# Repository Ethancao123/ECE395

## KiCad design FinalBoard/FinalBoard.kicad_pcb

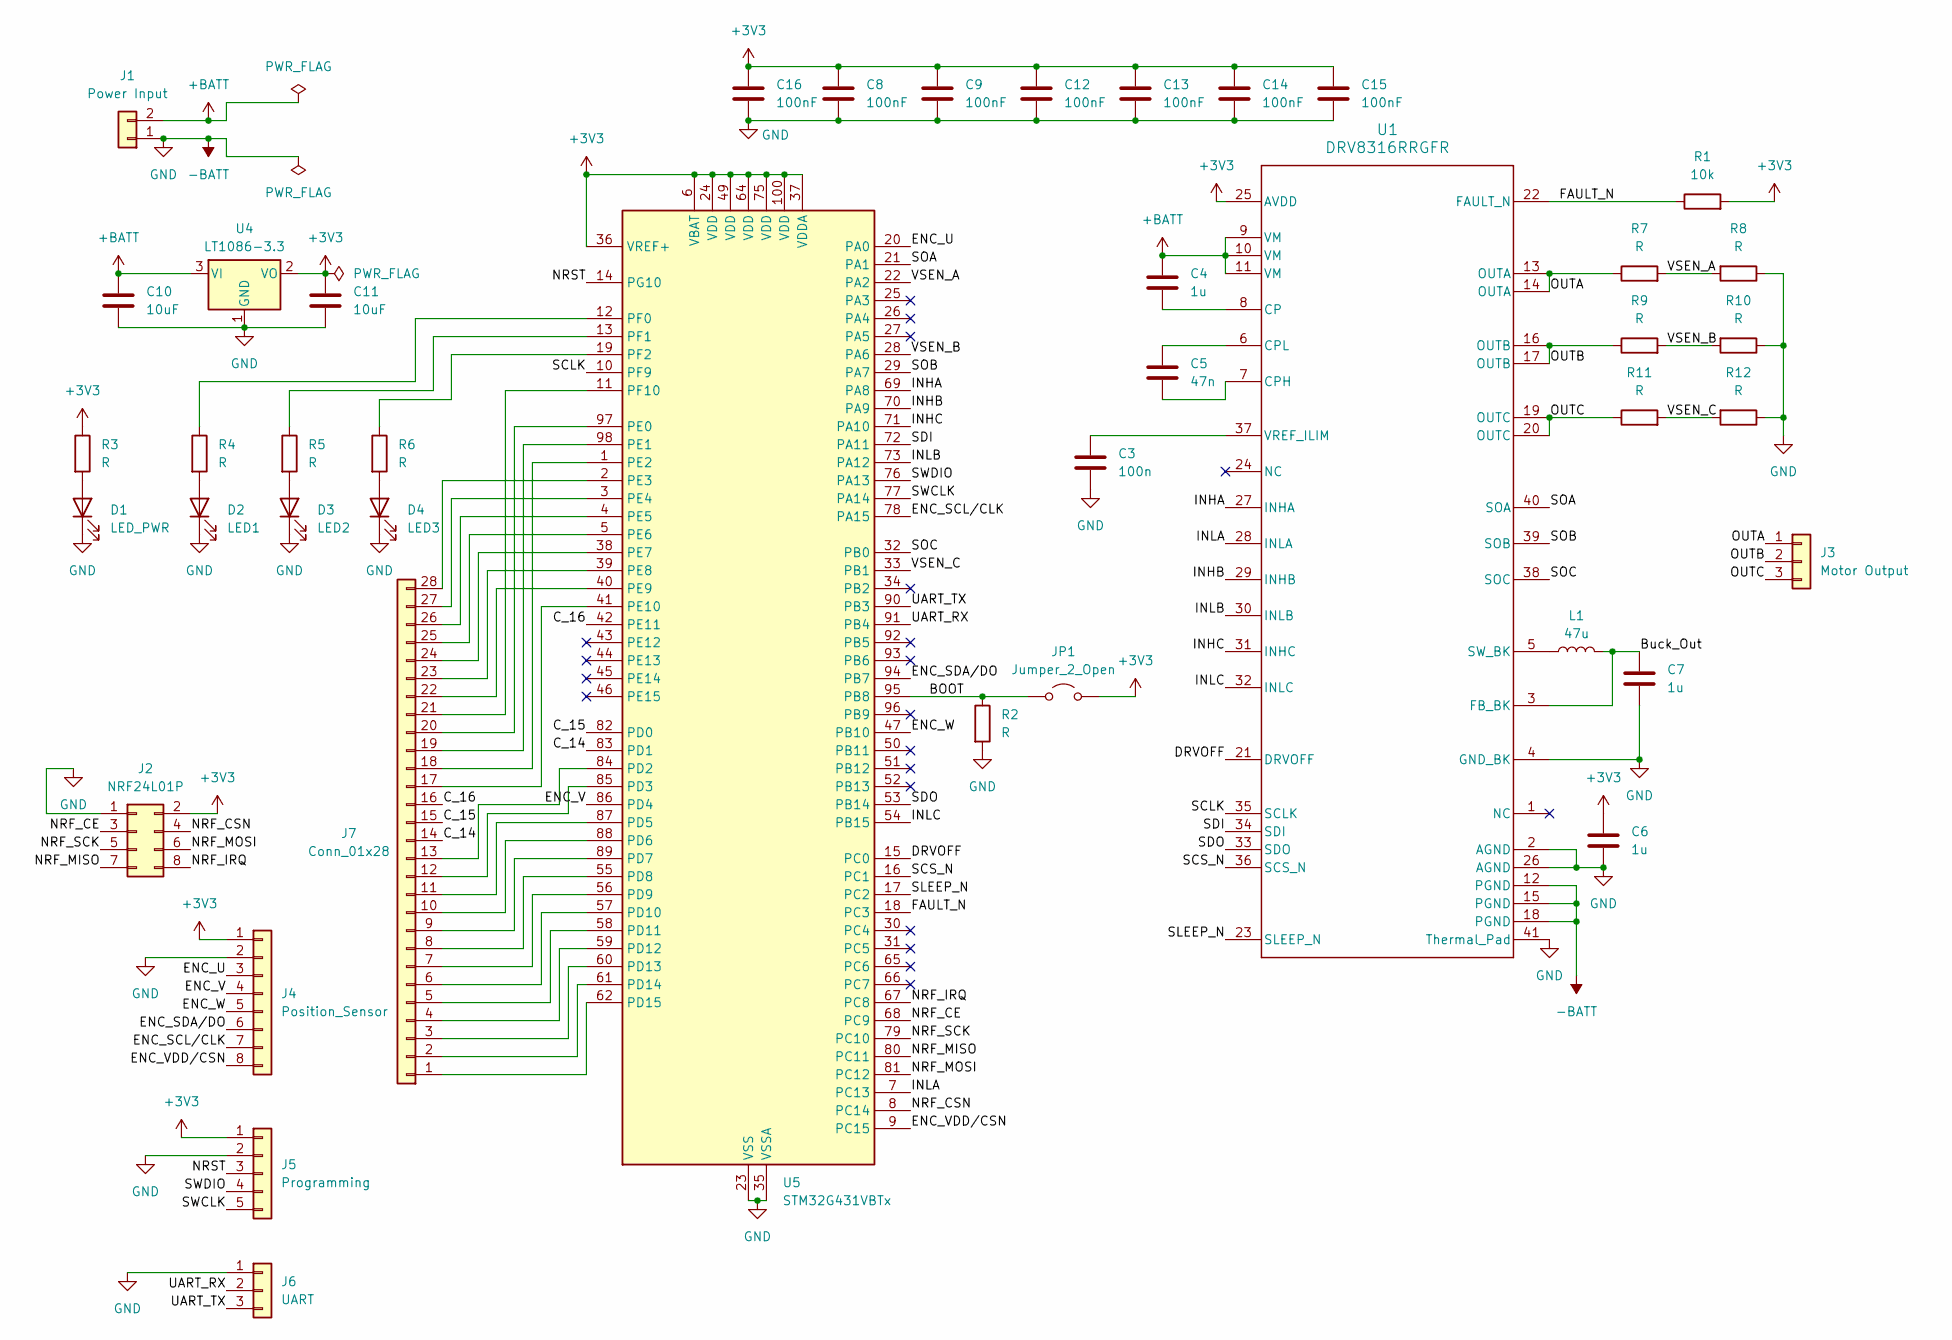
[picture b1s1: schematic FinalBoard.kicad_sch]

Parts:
C3: 100n; C_0805_2012Metric_Pad1.18x1.45mm_HandSolder
C4, C6, C7: 1u; C_0805_2012Metric_Pad1.18x1.45mm_HandSolder
C5: 47n; C_0805_2012Metric_Pad1.18x1.45mm_HandSolder
C8, C9, C12, C13, C14, C15, C16: 100nF; C_0805_2012Metric_Pad1.18x1.45mm_HandSolder
C10, C11: 10uF; CP_EIA-6032-28_Kemet-C_Pad2.25x2.35mm_HandSolder
D1: LED_PWR; LED_2512_6332Metric_Pad1.52x3.35mm_HandSolder
D2: LED1; LED_2512_6332Metric_Pad1.52x3.35mm_HandSolder
D3: LED2; LED_2512_6332Metric_Pad1.52x3.35mm_HandSolder
D4: LED3; LED_2512_6332Metric_Pad1.52x3.35mm_HandSolder
J1: Power Input; AMASS_XT30UPB-M_1x02_P5.0mm_Vertical
J2: NRF24L01P; PinHeader_2x04_P2.54mm_Vertical
J3: Motor Output; PinHeader_1x03_P2.54mm_Vertical
J4: Position_Sensor; PinHeader_1x08_P2.54mm_Vertical
J5: Programming; PinHeader_1x05_P2.54mm_Vertical
J6: UART; PinHeader_1x03_P2.54mm_Vertical
J7: Conn_01x28; PinHeader_1x28_P2.54mm_Vertical
JP1: Jumper_2_Open; SolderJumper-2_P1.3mm_Open_RoundedPad1.0x1.5mm
L1: 47u; L_0603_1608Metric
R1: 10k; R_0805_2012Metric_Pad1.20x1.40mm_HandSolder
R2, R3, R4, R5, R6, R7, R8, R9, R10, R11, R12: R; LED_0805_2012Metric_Pad1.15x1.40mm_HandSolder
U1: DRV8316RRGFR; RGF0040E-IPC_A
U4: LT1086-3.3; TO-220-3_Vertical
U5: STM32G431VBTx; LQFP-100_14x14mm_P0.5mm

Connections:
+3V3: C6.1, C8.1, C9.1, C11.1, C12.1, C13.1, C14.1, C15.1, C16.1, J2.2, J4.1, J5.1, JP1.2 (B), R1.2, R3.1, U1.25 (AVDD), U4.2 (VO), U5.6 (VBAT), U5.24 (VDD), U5.36 (VREF+), U5.37 (VDDA), U5.49 (VDD), U5.64 (VDD), U5.75 (VDD), U5.100 (VDD); also elsewhere on the board
+BATT: C4.1, C10.1, J1.2, U1.9 (VM), U1.10 (VM), U1.11 (VM), U4.3 (VI)
-BATT: C3.2, C6.2, C7.1, C8.2, C9.2, C10.2, C11.2, C12.2, C13.2, C14.2, C15.2, C16.2, D1.1 (K), D2.1 (K), D3.1 (K), D4.1 (K), J1.1, J2.1, J4.2, J5.2, J6.1, R2.2, R8.1, R10.1, R12.1, U1.2 (AGND), U1.4 (GND_BK), U1.12 (PGND), U1.15 (PGND), U1.18 (PGND), U1.26 (AGND), U1.41 (Thermal_Pad), U4.1 (GND), U5.23 (VSS), U5.35 (VSSA), U5.48 (VSS), U5.63 (VSS), U5.74 (VSS), U5.99 (VSS)
/BOOT: JP1.1 (A), R2.1, U5.95 (PB8); also elsewhere on the board
/Buck_Out: C7.2, L1.2, U1.3 (FB_BK)
/C_14: J7.14, U5.83 (PD1)
/C_15: J7.15, U5.82 (PD0)
/C_16: J7.16, U5.42 (PE11)
/DRVOFF: U1.21 (DRVOFF), U5.15 (PC0)
/ENC_SCL/CLK: J4.7, U5.78 (PA15)
/ENC_SDA/DO: J4.6, U5.94 (PB7)
/ENC_U: J4.3, U5.20 (PA0)
/ENC_V: J4.4, U5.86 (PD4)
/ENC_VDD/CSN: J4.8, U5.9 (PC15)
/ENC_W: J4.5, U5.47 (PB10)
/FAULT_N: R1.1, U1.22 (FAULT_N), U5.18 (PC3)
/INHA: U1.27 (INHA), U5.69 (PA8)
/INHB: U1.29 (INHB), U5.70 (PA9)
/INHC: U1.31 (INHC), U5.71 (PA10)
/INLA: U1.28 (INLA), U5.7 (PC13)
/INLB: U1.30 (INLB), U5.73 (PA12)
/INLC: U1.32 (INLC), U5.54 (PB15)
/NRF_CE: J2.3, U5.68 (PC9)
/NRF_CSN: J2.4, U5.8 (PC14)
/NRF_IRQ: J2.8, U5.67 (PC8)
/NRF_MISO: J2.7, U5.80 (PC11)
/NRF_MOSI: J2.6, U5.81 (PC12)
/NRF_SCK: J2.5, U5.79 (PC10)
/NRST: J5.3, U5.14 (PG10)
/OUTA: J3.1, R7.1, U1.13 (OUTA), U1.14 (OUTA)
/OUTB: J3.2, R9.1, U1.16 (OUTB), U1.17 (OUTB)
/OUTC: J3.3, R11.1, U1.19 (OUTC), U1.20 (OUTC)
/SCLK: U1.35 (SCLK), U5.10 (PF9)
/SCS_N: U1.36 (SCS_N), U5.16 (PC1)
/SDI: U1.34 (SDI), U5.72 (PA11)
/SDO: U1.33 (SDO), U5.53 (PB14)
/SLEEP_N: U1.23 (SLEEP_N), U5.17 (PC2)
/SOA: U1.40 (SOA), U5.21 (PA1)
/SOB: U1.39 (SOB), U5.29 (PA7)
/SOC: U1.38 (SOC), U5.32 (PB0)
/SWCLK: J5.5, U5.77 (PA14)
/SWDIO: J5.4, U5.76 (PA13)
/UART_RX: J6.2, U5.91 (PB4)
/UART_TX: J6.3, U5.90 (PB3)
/VSEN_A: R7.2, R8.2, U5.22 (PA2)
/VSEN_B: R9.2, R10.2, U5.28 (PA6)
/VSEN_C: R11.2, R12.2, U5.33 (PB1)
unnamed: D1.2 (A), R3.2
unnamed: D2.2 (A), R4.2
unnamed: D3.2 (A), R5.2
unnamed: D4.2 (A), R6.2
unnamed: J7.1, U5.62 (PD15)
unnamed: J7.2, U5.61 (PD14)
unnamed: J7.3, U5.60 (PD13)
unnamed: J7.4, U5.59 (PD12)
unnamed: J7.5, U5.58 (PD11)
unnamed: J7.6, U5.57 (PD10)
unnamed: J7.7, U5.56 (PD9)
unnamed: J7.8, U5.55 (PD8)
unnamed: J7.9, U5.89 (PD7)
unnamed: J7.10, U5.88 (PD6)
unnamed: J7.11, U5.87 (PD5)
unnamed: J7.12, U5.85 (PD3)
unnamed: J7.13, U5.84 (PD2)
unnamed: J7.17, U5.41 (PE10)
unnamed: J7.18, U5.1 (PE2)
unnamed: J7.19, U5.98 (PE1)
unnamed: J7.20, U5.97 (PE0)
unnamed: J7.21, U5.11 (PF10)
unnamed: J7.22, U5.40 (PE9)
unnamed: J7.23, U5.39 (PE8)
unnamed: J7.24, U5.38 (PE7)
unnamed: J7.25, U5.5 (PE6)
unnamed: J7.26, U5.4 (PE5)
unnamed: J7.27, U5.3 (PE4)
unnamed: J7.28, U5.2 (PE3)
unnamed: C4.2, U1.8 (CP)
unnamed: C5.2, U1.7 (CPH)
unnamed: C5.1, U1.6 (CPL)
unnamed: L1.1, U1.5 (SW_BK)
unnamed: C3.1, U1.37 (VREF_ILIM)
unnamed: R4.1, U5.12 (PF0)
unnamed: R5.1, U5.13 (PF1)
unnamed: R6.1, U5.19 (PF2)

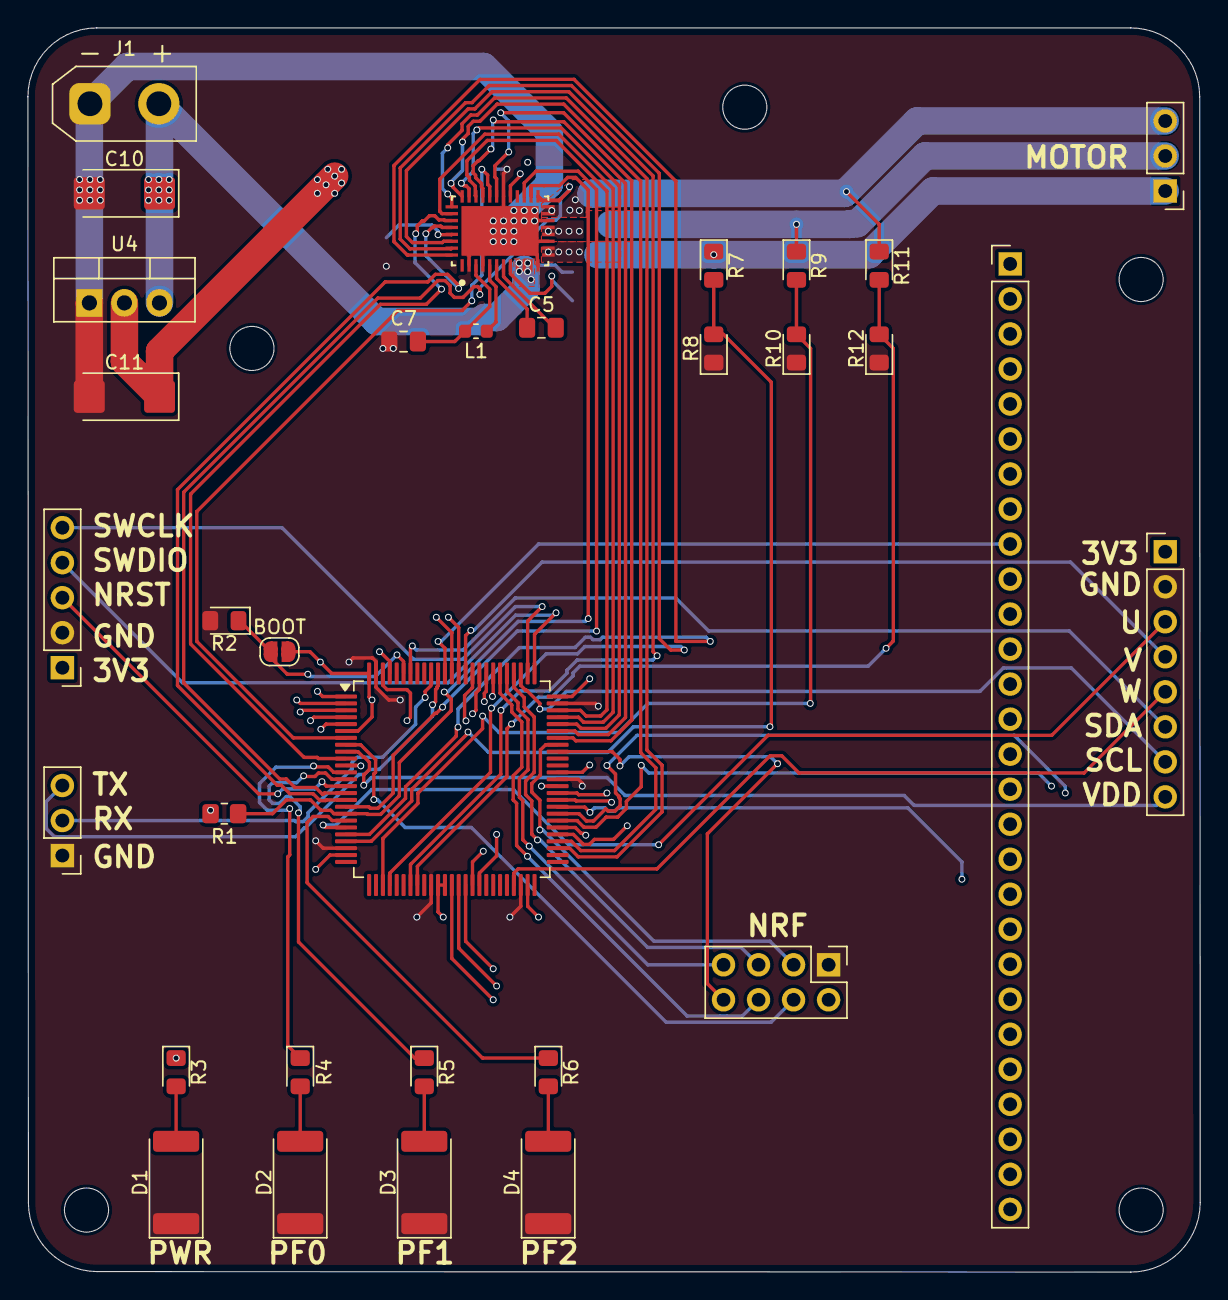
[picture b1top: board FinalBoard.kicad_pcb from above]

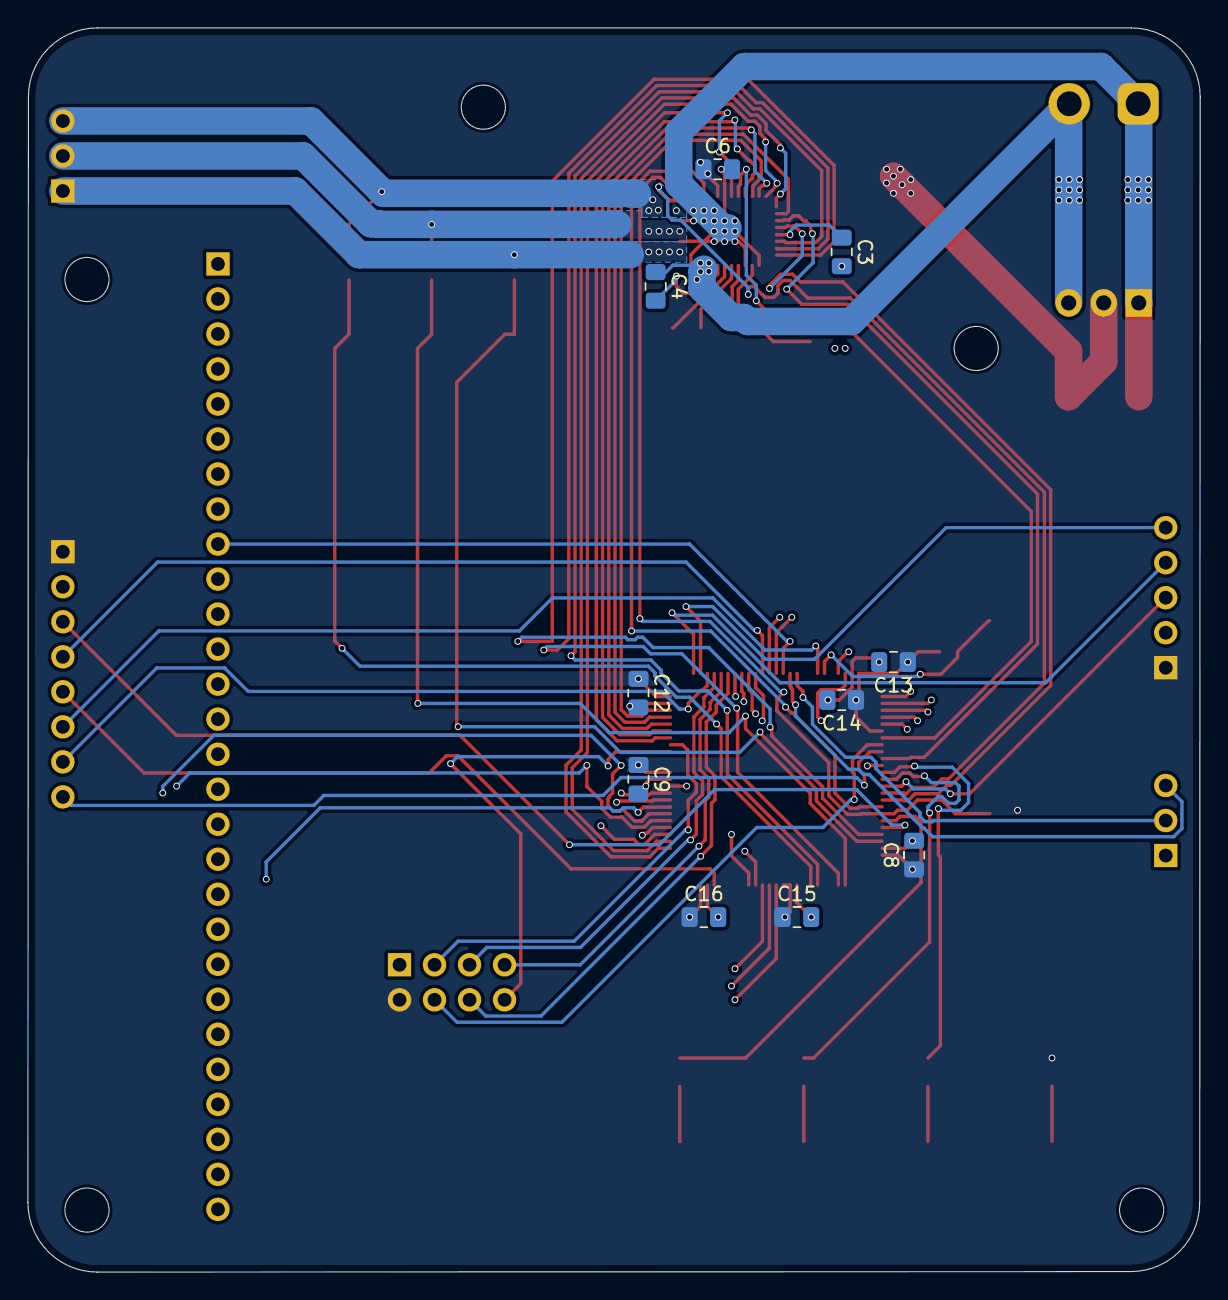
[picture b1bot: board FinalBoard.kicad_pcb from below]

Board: 4 copper layers, 85.0 x 90.2 mm, 42 parts (10 on the bottom side), 84 nets.

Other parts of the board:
BOOT: Jumper_2_Open; SolderJumper-2_P1.3mm_Open_RoundedPad1.0x1.5mm

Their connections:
+3V3: BOOT.2 (B); also elsewhere on the board
/BOOT: BOOT.1 (A); also elsewhere on the board

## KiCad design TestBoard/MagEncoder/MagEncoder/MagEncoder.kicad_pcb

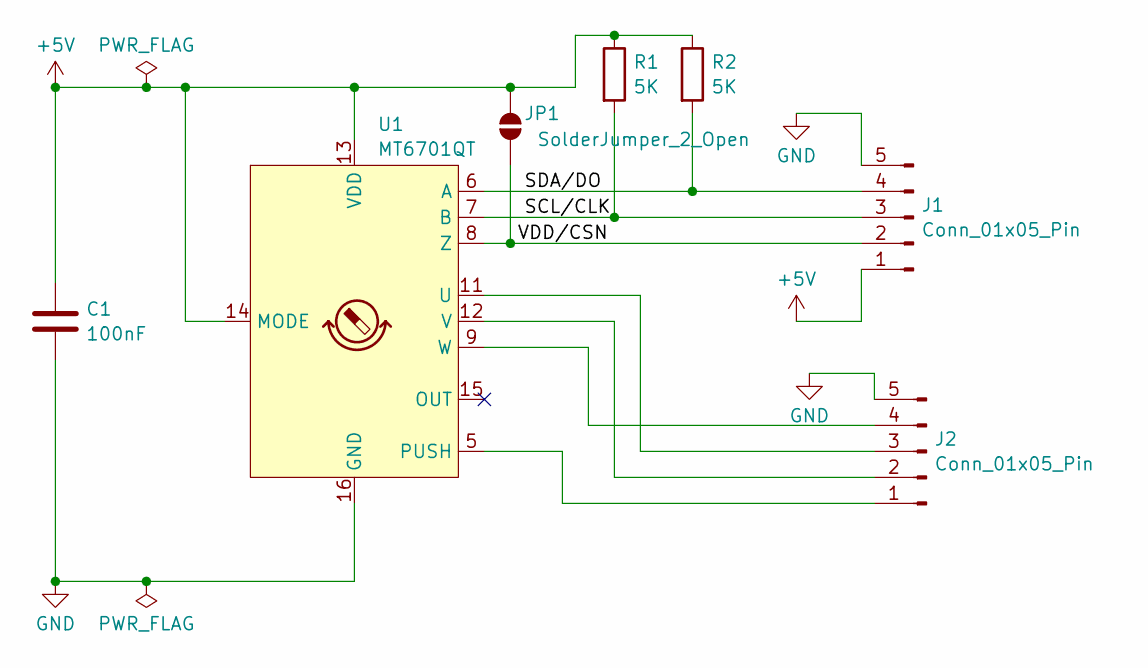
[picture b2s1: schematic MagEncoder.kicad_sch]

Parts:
C1: 100nF; C_0805_2012Metric_Pad1.18x1.45mm_HandSolder; LCSC Part Number C1525
J1, J2: Conn_01x05_Pin; JST_GH_SM05B-GHS-TB_1x05-1MP_P1.25mm_Horizontal; LCSC Part Number C189896
JP1: SolderJumper_2_Open; SolderJumper-2_P1.3mm_Bridged_RoundedPad1.0x1.5mm
R1, R2: 5K; R_0603_1608Metric_Pad0.98x0.95mm_HandSolder; LCSC Part Number C25905
U1: MT6701QT; QFN-16-1EP_3x3mm_P0.5mm_EP1.7x1.7mm; LCSC Part Number C2913974

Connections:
+5V: C1.1, J1.1, JP1.2 (B), R1.1, R2.1, U1.13 (VDD), U1.14 (MODE)
/SCL/CLK: J1.3, R1.2, U1.7 (B)
/SDA/DO: J1.4, R2.2, U1.6 (A)
/VDD/CSN: J1.2, JP1.1 (A), U1.8 (Z)
GND: C1.2, J1.5, J2.5, U1.16 (GND), U1.17 (GND)
unnamed: J2.1, U1.5 (PUSH)
unnamed: J2.2, U1.12 (V)
unnamed: J2.3, U1.11 (U)
unnamed: J2.4, U1.9 (W)

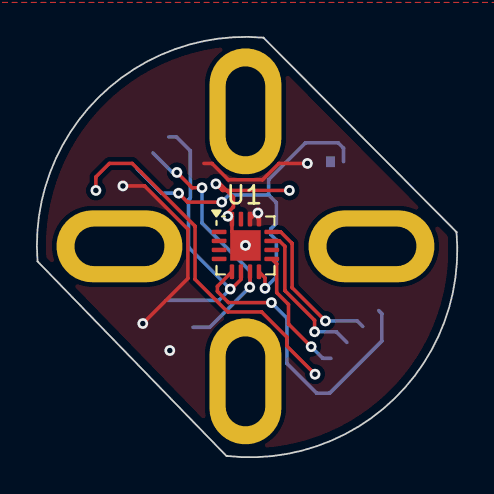
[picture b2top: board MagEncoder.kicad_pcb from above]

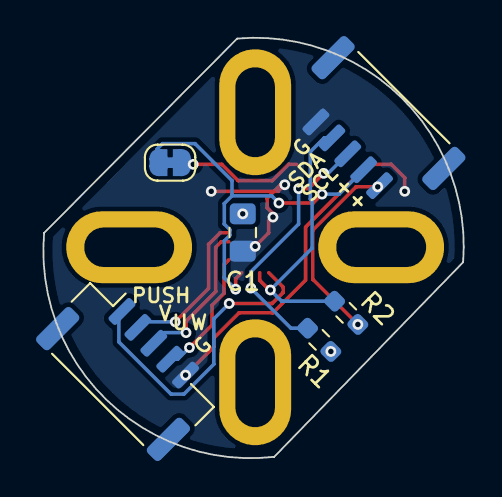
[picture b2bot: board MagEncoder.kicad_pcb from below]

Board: 2 copper layers, 23.4 x 23.3 mm, 7 parts (6 on the bottom side), 9 nets.

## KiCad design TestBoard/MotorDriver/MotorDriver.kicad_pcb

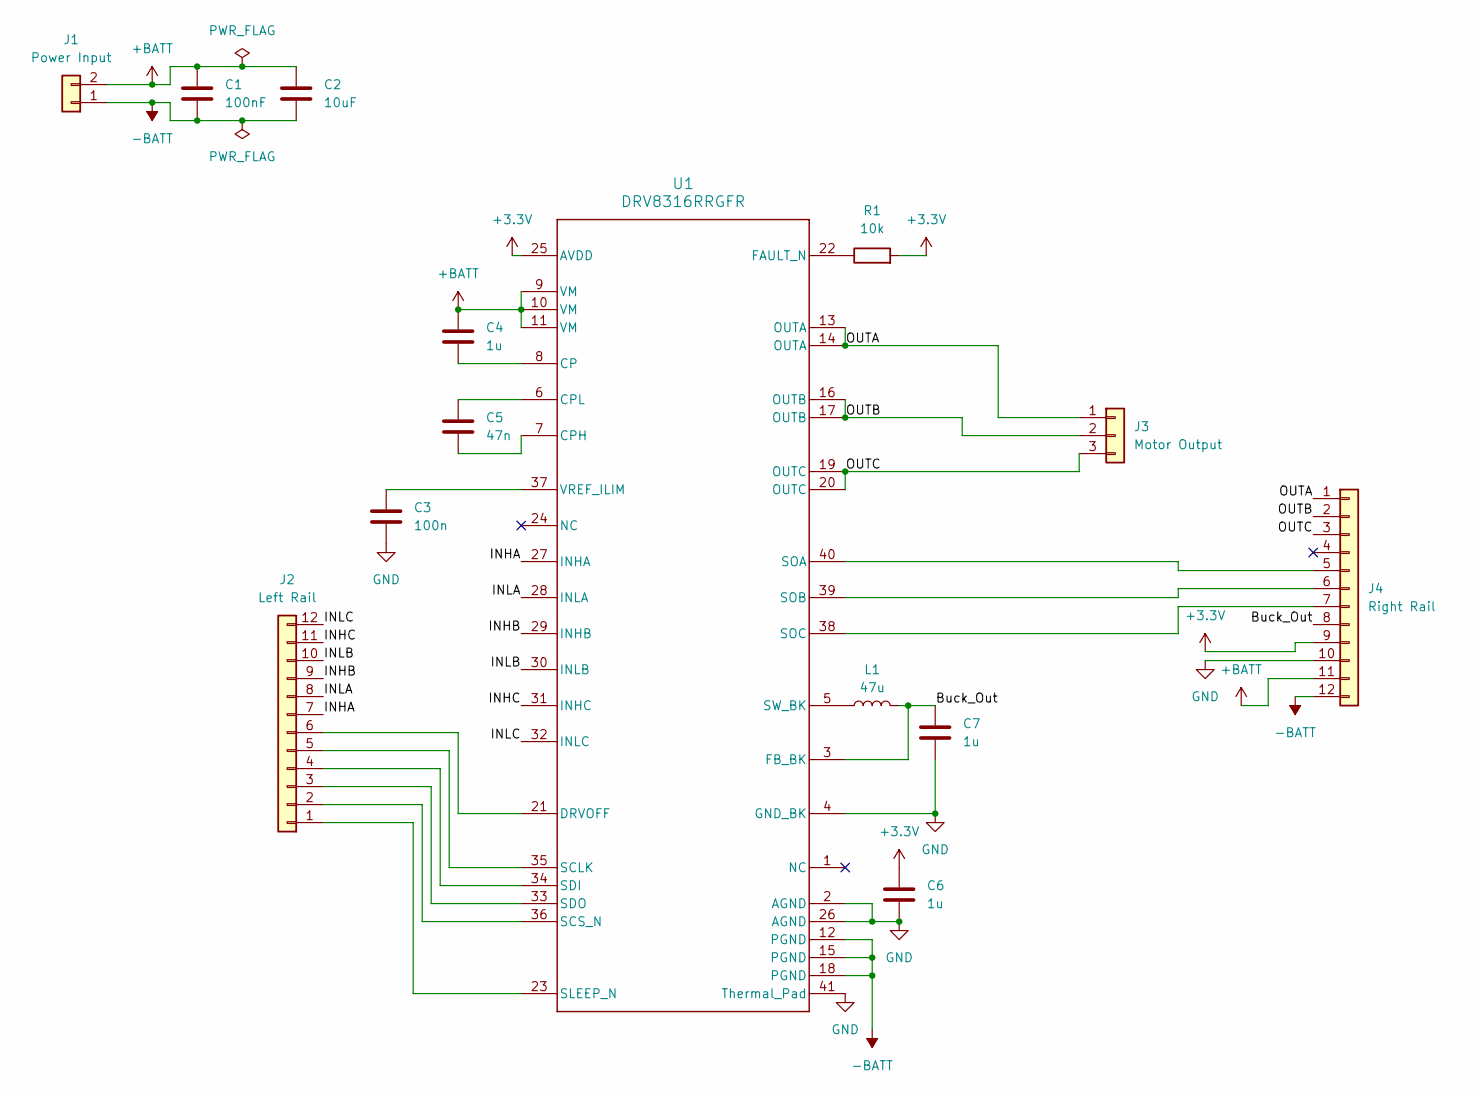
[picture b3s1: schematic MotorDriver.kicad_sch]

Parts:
C1: 100nF; C_0805_2012Metric_Pad1.18x1.45mm_HandSolder
C2: 10uF; C_0805_2012Metric_Pad1.18x1.45mm_HandSolder
C3: 100n; C_0805_2012Metric_Pad1.18x1.45mm_HandSolder
C4, C6, C7: 1u; C_0805_2012Metric_Pad1.18x1.45mm_HandSolder
C5: 47n; C_0805_2012Metric_Pad1.18x1.45mm_HandSolder
J1: Power Input; Power_Pads
J2: Left Rail; PinHeader_1x12_P2.54mm_Vertical
J3: Motor Output; Motor_Pads
J4: Right Rail; PinHeader_1x12_P2.54mm_Vertical
L1: 47u; L_0603_1608Metric
R1: 10k; R_0805_2012Metric_Pad1.20x1.40mm_HandSolder
U1: DRV8316RRGFR; RGF0040E-IPC_A

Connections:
+3.3V: C6.1, J4.9, R1.2, U1.25 (AVDD)
+BATT: C1.1, C2.1, C4.1, J1.2, J4.11, U1.9 (VM), U1.10 (VM), U1.11 (VM)
-BATT: C1.2, C2.2, J1.1, J4.12, U1.12 (PGND), U1.15 (PGND), U1.18 (PGND)
/Buck_Out: C7.2, J4.8, L1.2, U1.3 (FB_BK)
/INHA: J2.7, U1.27 (INHA)
/INHB: J2.9, U1.29 (INHB)
/INHC: J2.11, U1.31 (INHC)
/INLA: J2.8, U1.28 (INLA)
/INLB: J2.10, U1.30 (INLB)
/INLC: J2.12, U1.32 (INLC)
/OUTA: J3.1, J4.1, U1.13 (OUTA), U1.14 (OUTA)
/OUTB: J3.2, J4.2, U1.16 (OUTB), U1.17 (OUTB)
/OUTC: J3.3, J4.3, U1.19 (OUTC), U1.20 (OUTC)
GND: C3.2, C6.2, C7.1, J4.10, U1.2 (AGND), U1.4 (GND_BK), U1.26 (AGND), U1.41 (Thermal_Pad)
unnamed: J2.1, U1.23 (SLEEP_N)
unnamed: J2.2, U1.36 (SCS_N)
unnamed: J2.3, U1.33 (SDO)
unnamed: J2.4, U1.34 (SDI)
unnamed: J2.5, U1.35 (SCLK)
unnamed: J2.6, U1.21 (DRVOFF)
unnamed: J4.5, U1.40 (SOA)
unnamed: J4.6, U1.39 (SOB)
unnamed: J4.7, U1.38 (SOC)
unnamed: C4.2, U1.8 (CP)
unnamed: C5.2, U1.7 (CPH)
unnamed: C5.1, U1.6 (CPL)
unnamed: R1.1, U1.22 (FAULT_N)
unnamed: L1.1, U1.5 (SW_BK)
unnamed: C3.1, U1.37 (VREF_ILIM)

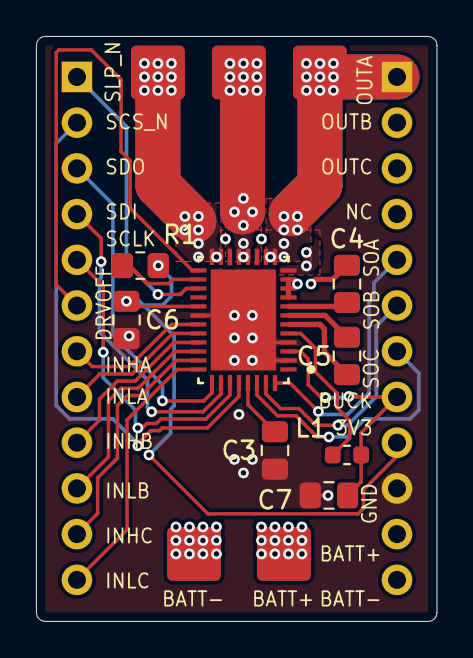
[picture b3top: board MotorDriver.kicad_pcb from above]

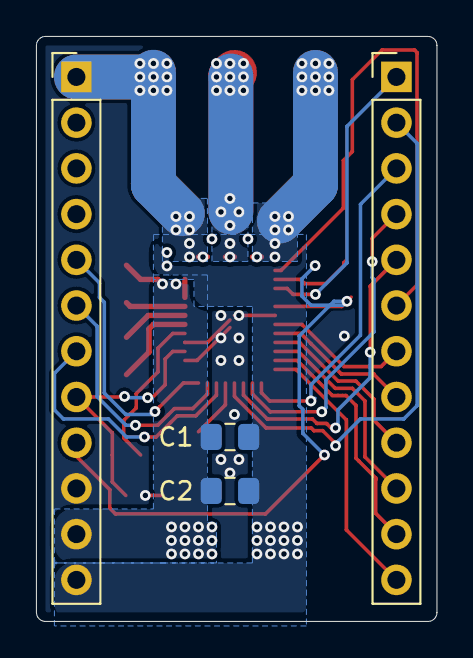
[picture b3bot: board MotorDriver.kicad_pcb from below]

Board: 4 copper layers, 22.2 x 32.5 mm, 14 parts (4 on the bottom side), 29 nets.

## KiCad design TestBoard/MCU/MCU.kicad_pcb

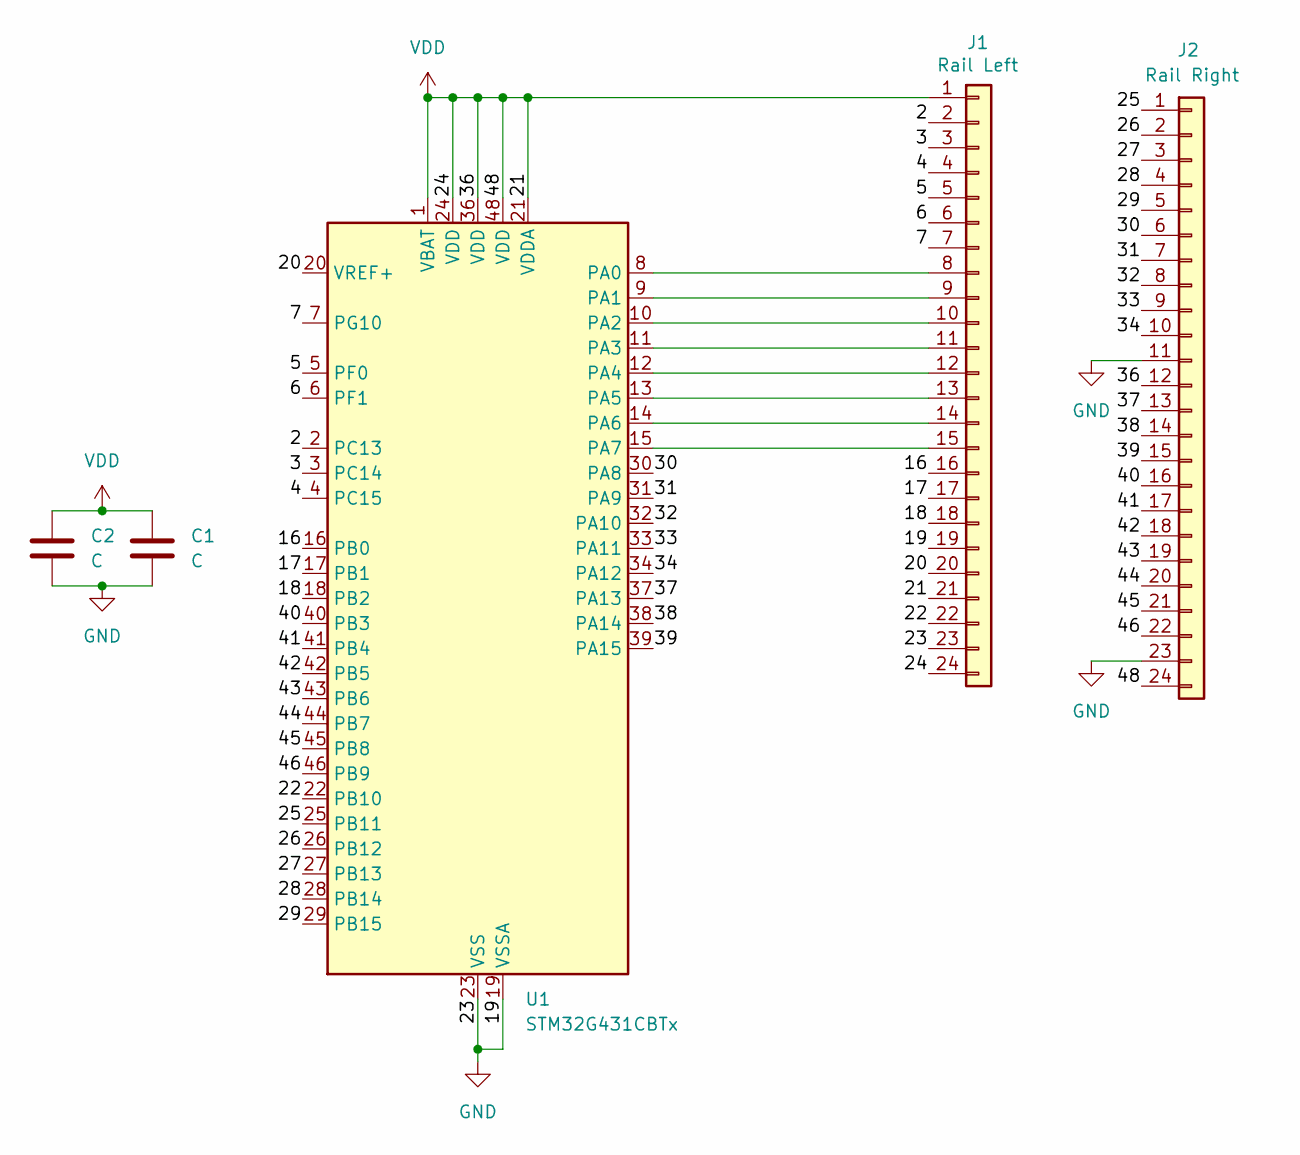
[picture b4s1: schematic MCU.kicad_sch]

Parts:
C1, C2: C; C_0603_1608Metric_Pad1.08x0.95mm_HandSolder
J1: Rail Left; PinHeader_1x24_P2.54mm_Vertical
J2: Rail Right; PinHeader_1x24_P2.54mm_Vertical
U1: STM32G431CBTx; LQFP-48_7x7mm_P0.5mm

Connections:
/2: J1.2, U1.2 (PC13)
/3: J1.3, U1.3 (PC14)
/4: J1.4, U1.4 (PC15)
/5: J1.5, U1.5 (PF0)
/6: J1.6, U1.6 (PF1)
/7: J1.7, U1.7 (PG10)
/16: J1.16, U1.16 (PB0)
/17: J1.17, U1.17 (PB1)
/18: J1.18, U1.18 (PB2)
/20: J1.20, U1.20 (VREF+)
/22: J1.22, U1.22 (PB10)
/25: J2.1, U1.25 (PB11)
/26: J2.2, U1.26 (PB12)
/27: J2.3, U1.27 (PB13)
/28: J2.4, U1.28 (PB14)
/29: J2.5, U1.29 (PB15)
/30: J2.6, U1.30 (PA8)
/31: J2.7, U1.31 (PA9)
/32: J2.8, U1.32 (PA10)
/33: J2.9, U1.33 (PA11)
/34: J2.10, U1.34 (PA12)
/37: J2.13, U1.37 (PA13)
/38: J2.14, U1.38 (PA14)
/39: J2.15, U1.39 (PA15)
/40: J2.16, U1.40 (PB3)
/41: J2.17, U1.41 (PB4)
/42: J2.18, U1.42 (PB5)
/43: J2.19, U1.43 (PB6)
/44: J2.20, U1.44 (PB7)
/45: J2.21, U1.45 (PB8)
/46: J2.22, U1.46 (PB9)
GND: C1.2, C2.2, J1.19, J1.23, J2.11, J2.23, U1.19 (VSSA), U1.23 (VSS), U1.35 (VSS), U1.47 (VSS)
unnamed: J1.8, U1.8 (PA0)
unnamed: J1.9, U1.9 (PA1)
unnamed: J1.10, U1.10 (PA2)
unnamed: J1.11, U1.11 (PA3)
unnamed: J1.12, U1.12 (PA4)
unnamed: J1.13, U1.13 (PA5)
unnamed: J1.14, U1.14 (PA6)
unnamed: J1.15, U1.15 (PA7)
VDD: C1.1, C2.1, J1.1, J1.21, J1.24, J2.12, J2.24, U1.1 (VBAT), U1.21 (VDDA), U1.24 (VDD), U1.36 (VDD), U1.48 (VDD)

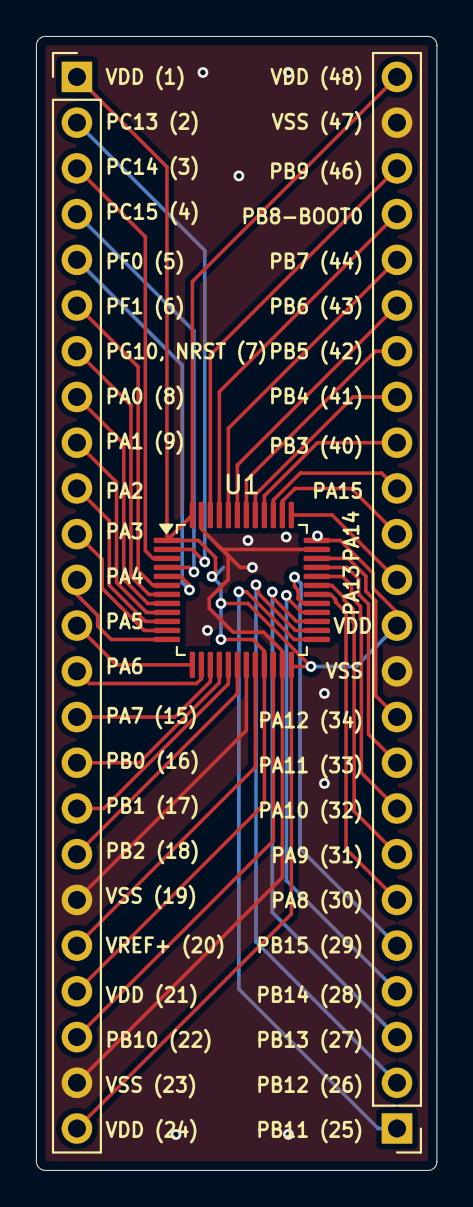
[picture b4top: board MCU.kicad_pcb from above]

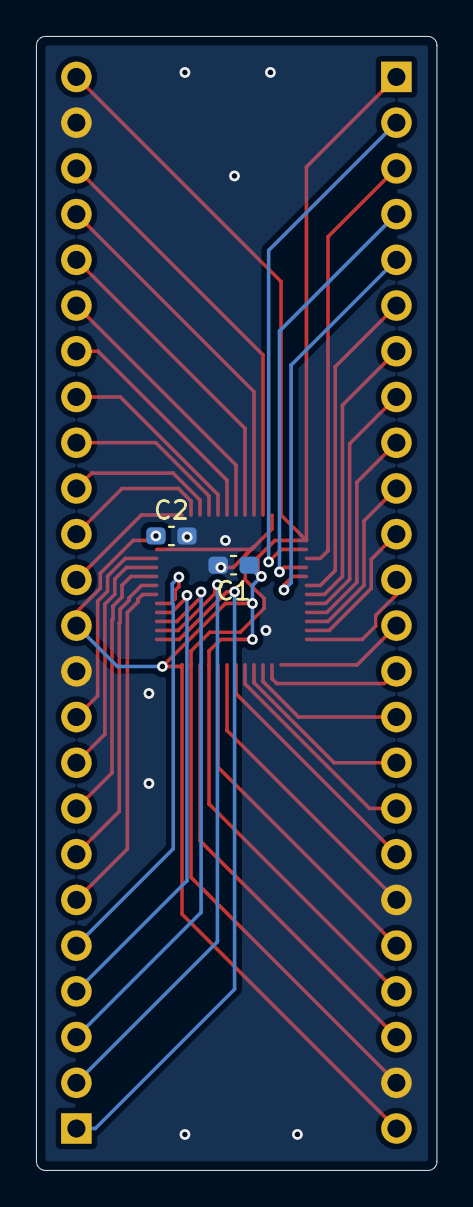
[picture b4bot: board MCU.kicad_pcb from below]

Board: 2 copper layers, 22.2 x 63.0 mm, 5 parts (2 on the bottom side), 41 nets.

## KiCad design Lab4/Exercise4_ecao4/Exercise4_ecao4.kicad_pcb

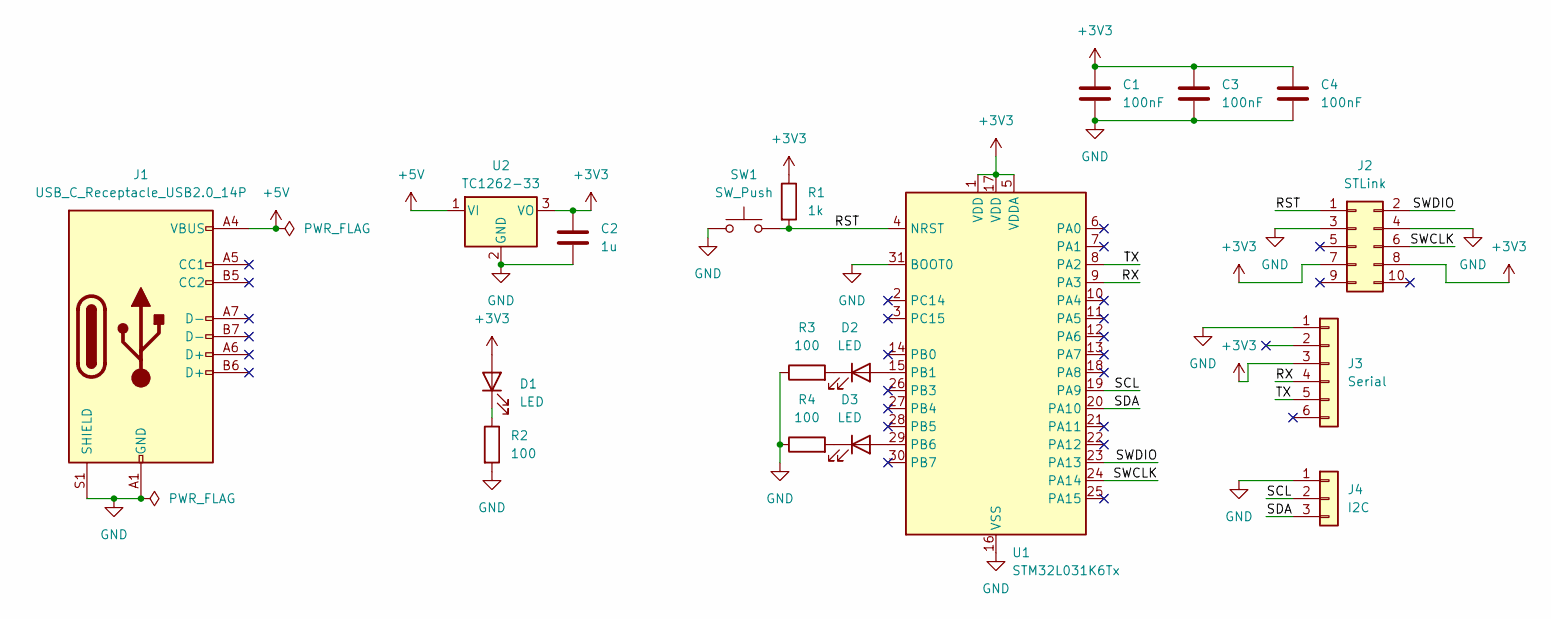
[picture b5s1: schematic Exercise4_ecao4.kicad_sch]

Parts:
C1, C3, C4: 100nF; C_0805_2012Metric_Pad1.18x1.45mm_HandSolder
C2: 1u; C_0805_2012Metric_Pad1.18x1.45mm_HandSolder
D1, D2, D3: LED; D_0805_2012Metric_Pad1.15x1.40mm_HandSolder
J1: USB_C_Receptacle_USB2.0_14P; USB_C_Receptacle_GCT_USB4085
J2: STLink; PinHeader_2x05_P2.54mm_Vertical
J3: Serial; PinHeader_1x06_P2.54mm_Vertical
J4: I2C; PinHeader_1x03_P2.54mm_Vertical
R1: 1k; C_0805_2012Metric_Pad1.18x1.45mm_HandSolder
R2, R3, R4: 100; C_0805_2012Metric_Pad1.18x1.45mm_HandSolder
SW1: SW_Push; SW_PUSH_6mm
U1: STM32L031K6Tx; LQFP-32_7x7mm_P0.8mm
U2: TC1262-33; TO-220-3_Vertical

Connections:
+3V3: C1.1, C2.1, C3.1, C4.1, D1.2 (A), J2.7, J2.8, J3.3, R1.1, U1.1 (VDD), U1.5 (VDDA), U1.17 (VDD), U2.3 (VO)
+5V: J1.A4 (VBUS), J1.A9 (VBUS), J1.B4 (VBUS), J1.B9 (VBUS), U2.1 (VI)
/RST: J2.1, R1.2, SW1.2, U1.4 (NRST)
/RX: J3.4, U1.9 (PA3)
/SCL: J4.2, U1.19 (PA9)
/SDA: J4.3, U1.20 (PA10)
/SWCLK: J2.6, U1.24 (PA14)
/SWDIO: J2.2, U1.23 (PA13)
/TX: J3.5, U1.8 (PA2)
GND: C1.2, C2.2, C3.2, C4.2, J1.A1 (GND), J1.A12 (GND), J1.B1 (GND), J1.B12 (GND), J1.S1 (SHIELD), J2.3, J2.4, J3.1, J4.1, R2.2, R3.1, R4.1, SW1.1, U1.16 (VSS), U1.31 (BOOT0), U1.32 (VSS), U2.2 (GND)
unnamed: D1.1 (K), R2.1
unnamed: D2.2 (A), U1.15 (PB1)
unnamed: D2.1 (K), R3.2
unnamed: D3.2 (A), U1.29 (PB6)
unnamed: D3.1 (K), R4.2

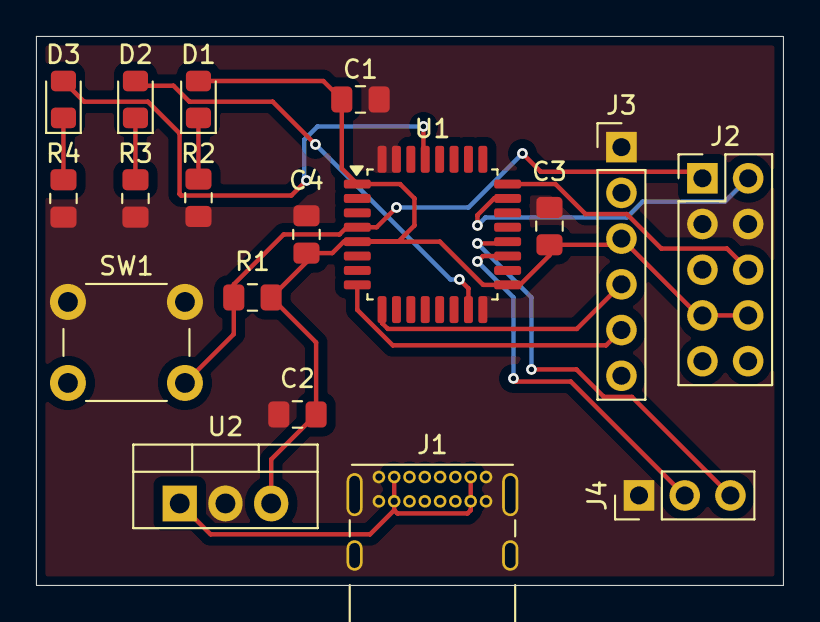
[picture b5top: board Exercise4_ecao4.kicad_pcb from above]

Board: 2 copper layers, 41.5 x 30.5 mm, 18 parts (0 on the bottom side), 15 nets.

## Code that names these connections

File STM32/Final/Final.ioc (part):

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Mcu.Name=STM32G431V(6-8-B)Tx
Mcu.Package=LQFP100
Mcu.UserName=STM32G431VBTx
PA1.Mode=IN2-Single-Ended
PA1.Signal=ADC1_IN2
PA10.Signal=S_TIM1_CH3
PA11.GPIOParameters=GPIO_Speed,GPIO_PuPd
PA11.GPIO_PuPd=GPIO_PULLDOWN
PA11.GPIO_Speed=GPIO_SPEED_FREQ_HIGH
PA11.Mode=Full_Duplex_Master
PA11.Signal=SPI2_MOSI
PA12.Mode=PWM Generation2 CH2 CH2N
PA12.Signal=TIM1_CH2N
PA13.Mode=Serial_Wire
PA13.Signal=SYS_JTMS-SWDIO
PA14.Mode=Serial_Wire
PA14.Signal=SYS_JTCK-SWCLK
PA15.Mode=I2C
PA15.Signal=I2C1_SCL
PA2.Mode=IN3-Single-Ended
PA2.Signal=ADC1_IN3
PA6.Mode=IN3-Single-Ended
PA6.Signal=ADC2_IN3
PA7.Mode=IN4-Single-Ended
PA7.Signal=ADC2_IN4
PA8.Signal=S_TIM1_CH1
PA9.Signal=S_TIM1_CH2
PB0.Mode=IN15-Single-Ended
PB0.Signal=ADC1_IN15
PB1.Mode=IN12-Single-Ended
PB1.Signal=ADC1_IN12
PB14.GPIOParameters=GPIO_Speed,GPIO_PuPd
PB14.GPIO_PuPd=GPIO_PULLUP
PB14.GPIO_Speed=GPIO_SPEED_FREQ_HIGH
PB14.Mode=Full_Duplex_Master
PB14.Signal=SPI2_MISO
PB15.Mode=PWM Generation3 CH3 CH3N
PB15.Signal=TIM1_CH3N
PB3.Mode=Asynchronous
PB3.Signal=USART2_TX
PB4.Mode=Asynchronous
PB4.Signal=USART2_RX
PB7.Mode=I2C
PB7.Signal=I2C1_SDA
PC0.GPIOParameters=GPIO_Label
PC0.GPIO_Label=DRVOFF
PC0.Signal=GPIO_Output
PC1.GPIOParameters=GPIO_Label
PC1.GPIO_Label=SCS_N
PC1.Signal=GPIO_Output
PC10.Mode=Full_Duplex_Master
PC10.Signal=SPI3_SCK
PC11.Mode=Full_Duplex_Master
PC11.Signal=SPI3_MISO
PC12.Mode=Full_Duplex_Master
PC12.Signal=SPI3_MOSI
PC13.Mode=PWM Generation1 CH1 CH1N
PC13.Signal=TIM1_CH1N
PC14-OSC32_IN.GPIOParameters=GPIO_Label
PC14-OSC32_IN.GPIO_Label=NRF_CSN
PC14-OSC32_IN.Signal=GPIO_Output
PC2.GPIOParameters=GPIO_Label
PC2.GPIO_Label=SLEEP_N
PC2.Signal=GPIO_Output
PC3.GPIOParameters=GPIO_Label
PC3.GPIO_Label=FAULT_N
PC3.Signal=GPIO_Input
PC9.GPIOParameters=GPIO_Label
PC9.GPIO_Label=NRF_CE
PC9.Signal=GPIO_Output
PF9.GPIOParameters=GPIO_Speed,GPIO_PuPd
PF9.GPIO_PuPd=GPIO_PULLDOWN
PF9.GPIO_Speed=GPIO_SPEED_FREQ_HIGH
PF9.Mode=Full_Duplex_Master
PF9.Signal=SPI2_SCK
RCC.HSE_VALUE=8000000
RCC.SYSCLKFreq_VALUE=16000000
board=custom

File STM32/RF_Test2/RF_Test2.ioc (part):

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Mcu.Name=STM32L031K(4-6)Tx
Mcu.Package=LQFP32
Mcu.UserName=STM32L031K6Tx
PA3.GPIOParameters=GPIO_Speed,PinState,GPIO_Label
PA3.GPIO_Label=CSN
PA3.GPIO_Speed=GPIO_SPEED_FREQ_HIGH
PA3.PinState=GPIO_PIN_SET
PA3.Signal=GPIO_Output
PA4.GPIOParameters=GPIO_Speed,GPIO_Label
PA4.GPIO_Label=CE
PA4.GPIO_Speed=GPIO_SPEED_FREQ_HIGH
PA4.Signal=GPIO_Output
PA5.Mode=Full_Duplex_Master
PA5.Signal=SPI1_SCK
PA6.Mode=Full_Duplex_Master
PA6.Signal=SPI1_MISO
PA7.Mode=Full_Duplex_Master
PA7.Signal=SPI1_MOSI
PA8.GPIOParameters=GPIO_PuPd,GPIO_Label
PA8.GPIO_Label=BTN
PA8.GPIO_PuPd=GPIO_PULLUP
PA8.Signal=GPIO_Input
PA9.GPIOParameters=GPIO_Label
PA9.GPIO_Label=LED2
PA9.Signal=GPIO_Output
PB1.GPIOParameters=GPIO_Label
PB1.GPIO_Label=LED
PB1.Signal=GPIO_Output
RCC.HSE_VALUE=8000000
RCC.SYSCLKFreq_VALUE=2097000
board=custom

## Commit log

2025-02-17 Motor Controller PCB Done
2025-02-17 MCU Done
2025-02-17 Labeled motor driver
2025-02-25 Gerbers
2025-02-25 STM32 Code
2025-02-25 TX-RX Test
2025-02-25 Wireless Worky
2025-02-25 Regen hardware for button
2025-03-06 Mag Encoder Done
2025-03-10 extend to 8 bits
2025-03-10 LED test worky!
2025-03-10 Add another LED Pin
2025-04-02 Final PCB Done
2025-04-08 Position sensor worky
2025-04-18 added simplefoc
2025-04-18 more porting
2025-04-30 Motor Twitches
2025-04-30 smooth motor!
2025-05-06 save
2025-05-06 Demoed!
2025-06-08 DONE!
